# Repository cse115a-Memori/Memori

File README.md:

# File Structure

`./memori-app` - Tauri code

`./memori-dev` - ESP32 code

`./doc` - Documents for class

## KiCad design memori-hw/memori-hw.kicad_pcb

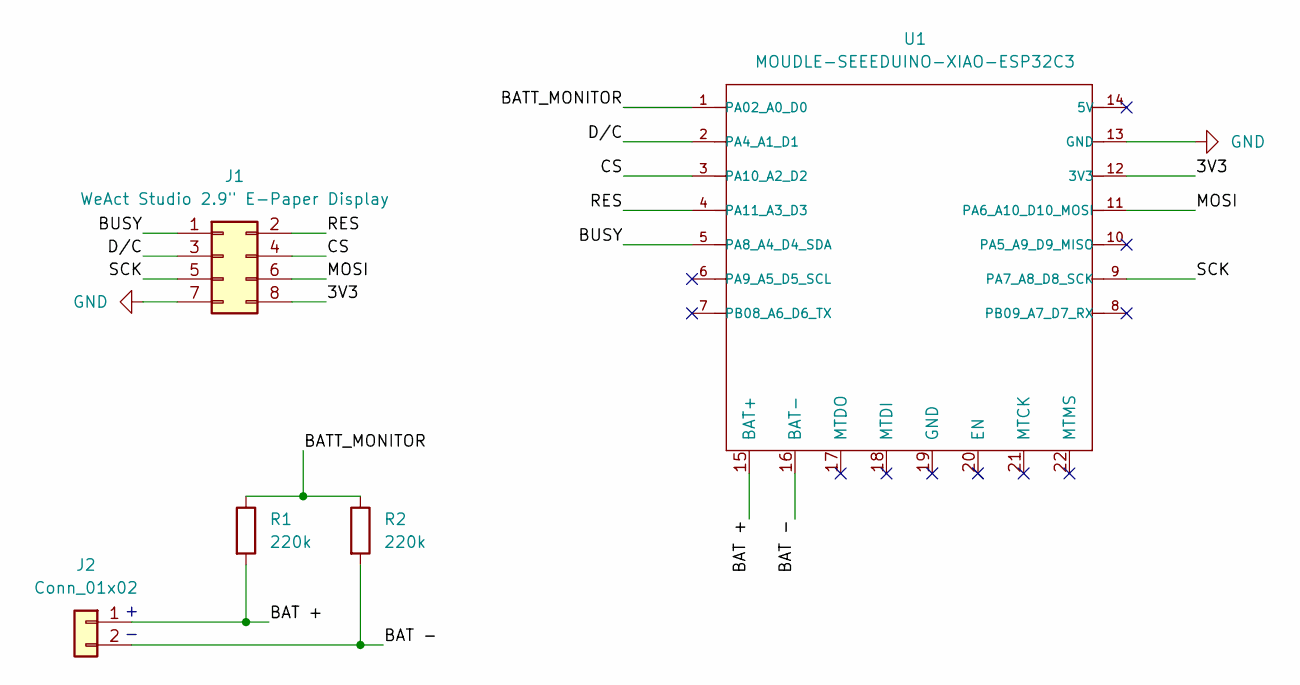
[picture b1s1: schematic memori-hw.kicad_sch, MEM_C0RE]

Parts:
J1: WeAct Studio 2.9" E-Paper Display; PinHeader_2x04_P2.54mm_Vertical
J2: Conn_01x02; JST_PH_S2B-PH-K_1x02_P2.00mm_Horizontal
R1, R2: 220k; R_Axial_DIN0204_L3.6mm_D1.6mm_P7.62mm_Horizontal
U1: MOUDLE-SEEEDUINO-XIAO-ESP32C3; XIAO-ESP32C3-SMD

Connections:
/3V3: J1.8, U1.12 (3V3)
/BAT +: J2.1, R1.2, U1.15 (BAT+)
/BAT -: J2.2, R2.2, U1.16 (BAT-)
/BATT_MONITOR: R1.1, R2.1, U1.1 (PA02_A0_D0)
/BUSY: J1.1, U1.5 (PA8_A4_D4_SDA)
/CS: J1.4, U1.3 (PA10_A2_D2)
/D/C: J1.3, U1.2 (PA4_A1_D1)
/MOSI: J1.6, U1.11 (PA6_A10_D10_MOSI)
/RES: J1.2, U1.4 (PA11_A3_D3)
/SCK: J1.5, U1.9 (PA7_A8_D8_SCK)
GND: J1.7, U1.13 (GND)

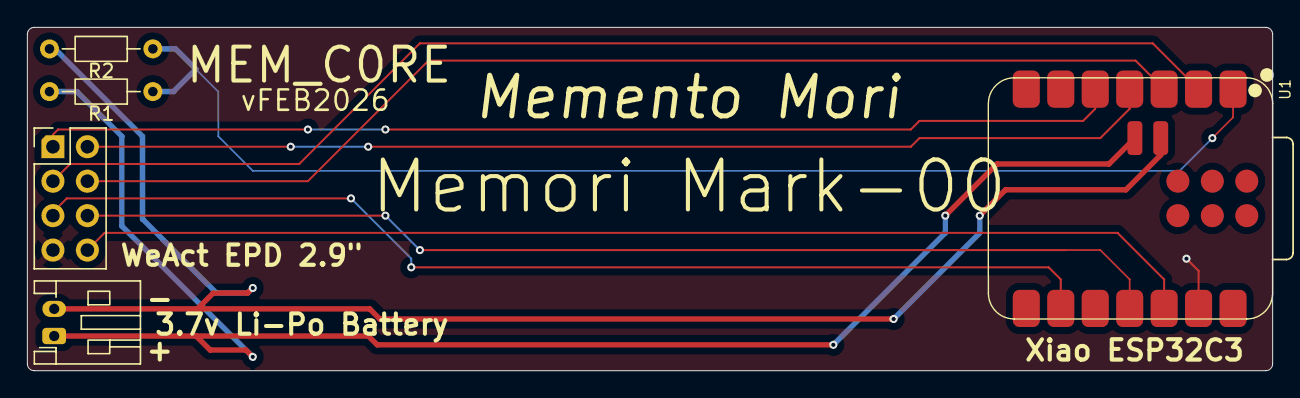
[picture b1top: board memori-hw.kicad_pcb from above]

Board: 4 copper layers, 91.8 x 25.3 mm, 5 parts (0 on the bottom side), 11 nets.

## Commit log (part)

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2026-01-09 added jj
2026-01-09 typst setup
2026-01-09 Added releaseplan files
2026-01-09 justfile
2026-01-10 esp project setup
2026-01-10 tauri setup
2026-01-10 tauri ios setup
2026-01-10 ESP32 setup
2026-01-10 justfile commands & readme
2026-01-10 setup mousefood
2026-01-11 fix readme & justfile
2026-01-11 setup svelte formatters
2026-01-11 new branch for me
2026-01-11 display hello world
2026-01-11 fixed typo
2026-01-14 Flake.nix
2026-01-15 Release plan
2026-01-16 more work on release plan
2026-01-17 finished with release plan
2026-01-17 example simulator
    basic simulator
2026-01-19 esp32c3 and simulator up and running
2026-01-19 restructuring
    something
2026-01-19 esp32c3 and simulator running memori
    pr fixes
2026-01-19 got tauri to run on ios device
2026-01-19 shadcn components
2026-01-20 fixed build errors and idomatic justfile
2026-01-20 added memori-transport
2026-01-21 add deepwiki badge
2026-01-23 display works on xiao
2026-01-25 taurpc
2026-01-25 svelte config fixup
2026-01-25 Added basic types for transport
2026-01-25 remade the memori-transport crates
2026-01-25 added the ble and websocket crates
2026-01-25 async traits
2026-01-25 setting up tcp transport
    we have some sort of communication so far
2026-01-25 async traits now constrain future to be boxed
2026-01-25 transport ble dependencies + esp ble test
2026-01-25 refactor tcp to be better
2026-01-25 tcp sim integration
2026-01-25 tcp app integration
2026-01-25 basic battery messaging
2026-01-25 patch fixes
2026-01-25 connect to simulator and get data back!
2026-01-26 fixes
2026-01-26 sprint1 plan
2026-01-28 Added Clock struct to widgets, and modified the esp update display function to properly increment the time
2026-01-28 Attempted to get the simulator to work with my widget. I think I am using the wrong commands to run it
2026-01-28 sprint1 report
2026-01-29 request_handler rework
2026-01-29 initial ble transport layer
    code enabling ble communication between the embedded board using
    transport/ble-device, and a host running the example binary provided
    through ble-host
    to test it out run the main binary on your board, then once it's
    advertising run the host-ble example "host"
2026-01-29 using oneshots
2026-01-29 rethink widget datamodel
2026-02-01 sprint 2 plan
2026-02-01 modified sprint 2 plan
2026-02-02 Added clock widget in current design
2026-02-02 Added clock to simulator's response to getBatteryLevel
2026-02-02 Added a bit of styling for the clock widget
2026-02-02 Delete memori-dev/memori/src/clock.rs
    I realized I had left this file in the branch on accident. It was from before we had the UI folder
2026-02-03 concurrent request support + refactoring
2026-02-04 non architecture dependant blepacket.id + other glorious ai suggested fixes
    title + typo fixes, no panicking in btleplug code, external timeout on
    devicebletransport
2026-02-04 more ergonomic external timeout for devicetransport
2026-02-04 ble interface
2026-02-04 device-side command concurrency
2026-02-04 remove cargo lock
2026-02-04 remove tracing
2026-02-05 initial run for local widget update task
2026-02-05 add device command and fix build for esp
2026-02-06 feat(memori-ui): Layout / Widget representation between app / device.
2026-02-06 fix compile for esp32
2026-02-06 refactor(memori-esp32): Refactor of BLE and UI for board.
2026-02-07 migrate to specta done
2026-02-07 remove unused test fn example
2026-02-07 dedup lib.rs imports
2026-02-07 cleanup and ble host import, to be implemented
2026-02-07 comment broken code out
2026-02-07 feat(memori-dev): Cancellable Refresh Tasks for Refreshable Widgets
2026-02-08 Esp now can spawn tasks to locally update any widget which sets local update frequency.
2026-02-08 fix(task-refrseh): Fixed static cell reinit issue via generation counter.
2026-02-09 learning dnd
2026-02-09 connecting app to board
2026-02-09 Local update frequency working with new widget framework. Will create a PR soon
2026-02-10 Removed extra logging statements
2026-02-10 Added github widget file. Need to flesh out rendering, and then work on state updating
2026-02-10 Github widget ui works for every layout. Need to consider what information we want to display though
2026-02-10 added bus and weather to tauri backend
2026-02-11 fixed specta in lib.rs for mobile, exclude type export
2026-02-11 connection type choice in app + ble-host cleanup
2026-02-11 sprint2 report and sprint3plan
2026-02-11 fix: Tauri send_name function now sends name.
2026-02-11 added layout and memoristate type export
2026-02-12 Adjusted dependencies
2026-02-12 Slight cleanup, added never variant to UpdateFrequency enum.
2026-02-12 Made clock borders the same as other widget borders
2026-02-12 added oauth flow
2026-02-12 removed file
2026-02-16 expose ble handler logic like tcp transport
2026-02-17 impl ble-host set state
2026-02-17 added commit graph to github widget. Need to slightly improve it and make sure it works for every layout.
2026-02-18 fixed typing issues in ble_host handler
2026-02-18 feat(hw): Init KiCad pcb design.
2026-02-18 oauth flow
2026-02-18 fixed 401 err with login
2026-02-19 very small changes to get app running without compile errors
2026-02-19 feat(hw): Finished with schematic.
2026-02-19 a lot of type gymnastics, dynamic layout done
2026-02-19 state scaffolding and dnd state, merged success with julian main
2026-02-19 generate bindings
2026-02-19 test run ios works
    checkpoint
2026-02-19 feat(hw): Finished non-battery PCB.
2026-02-20 Finished github widget UI
2026-02-20 Slight cleanup
2026-02-20 Made commits take an unsigned int because they can never be negative.
2026-02-20 Cleaned up some weird things that happened after merging the github widget.
2026-02-20 Removed unused imports and edited ble host_handler to utilize newer updatefrequency widgetKind member.
2026-02-20 feat(hw): Finished battery schematic.
2026-02-20 ios boot working, lots of refactoring
2026-02-21 simplify stores/services, extract location flow
2026-02-25 finalized sprint 3 report and sprint 4 plan
2026-02-25 revised
2026-02-26 added twitch
2026-02-26 small change to send_github
2026-02-28 refactor: gitignoring hw files.
2026-02-28 specta feature flags + suri fix(conn): name widget can now send to device and tcp
2026-02-28 tested to send widget payload over tcp and ble, simulator display update works, ble gets payload but no screen update
2026-02-28 scaffold connection update from rust, if ble wants to emit changes in connection state
2026-03-02 added github_data logic, need to finish up.
2026-03-02 refresh
2026-03-02 testing refresh over ble
2026-03-02 cargo path mismatch
2026-03-02 remove unused tcpconnection
2026-03-02 quick update
2026-03-02 per widget edit
2026-03-02 dnd logic bug fix
2026-03-02 break components apart, rename variables, combine widget + draft store
2026-03-02 edit each widget, refactor sortable item
2026-03-03 WidgetKind->Id, functions renamed and moved
2026-03-03 oauth refactor
2026-03-03 Trying my absolut best to get the test working. Realized I need to store Repo in tauri store in addition to username and auth token. Also, made the github widget repo not optional.
2026-03-03 accessed the tauri store from backend instead of frontend.
2026-03-04 changed test from getting commit frequency to refreshing the github widget.
2026-03-04 Cannot get stores from the backend.
2026-03-04 finally got auth token from store in the backend. Need to adjust the commit frequency array that I am receiving.
2026-03-04 need to fix commit frequency array
2026-03-05 Made sure to check all HTTP response status. Made helper function which all functions go through to actually do the HTTP requests.
2026-03-05 accidentally forgot to commit this to the PR, adding now
2026-03-05 tested app to run on ios phone, connects to esp over ble, set widget working, added some sound effects for connection success/failure
2026-03-05 add some sound effects
2026-03-05 feat/onboard: random device id generation on build stored statically
2026-03-06 feat/onboard: pairing widget displaying code
2026-03-06 feat/onboard: device advertises memori-{code}
2026-03-06 feat/onboard: app connects to memori-{code}
2026-03-06 add github persisted store
2026-03-06 initial ble refresh design impl
2026-03-06 mod dec i forgor from last commit
2026-03-06 Adjusted data.rs to utilize my refresh_github_widget function rather than the resolve_github_data function. Also made repo optional and handled cases where a user has not selected a repo yet.
2026-03-07 fixed dependency bug plus github login button.
2026-03-07 Finally got the frontend to receive updated information about current github login, and it reflects on the github widget tile.
2026-03-07 refactored github_data.rs to use a full_name repo rather than owner + repo strings. Also grabbed repo from Github store.
2026-03-07 Finalized github widget data resolution. Added dropdown menu for user's repos. Widget tile on frontend reflects choice.
2026-03-08 Added default for github_widget and stopped failing entire get_widget_kinds just for github fail.
2026-03-08 refactor
2026-03-08 modified Weather::new()
2026-03-08 modified oauth.rs
2026-03-08 added read:org to github auth scope
2026-03-08 refactor: organize documents
2026-03-08 feat: template for release summary
2026-03-08 feat: template for testplan
2026-03-08 feat: added all testable user stories to testplan
2026-03-08 simplify dnd logic, no cancel
2026-03-08 doc: worked on sprint4report, release-summary, testplan
2026-03-09 working on onboarding
2026-03-09 widget ui refactor
2026-03-09 updating but not rendering :(
2026-03-09 final commit before merge
2026-03-10 minimal onboard
    bg circle
    theme
2026-03-10 app working again, restore tauri-store version
2026-03-10 these are some fucky wucky changes
2026-03-10 ok we're here
2026-03-10 rust no compile error, app broken
2026-03-10 esp main typo fix
2026-03-10 pairing code
2026-03-10 feat/onboard: pairing code is now numeric
2026-03-10 sent working
2026-03-10 bus and weather
2026-03-11 feat/ui: HSplit, VSplit fixed
2026-03-11 device code saved, auto connects
2026-03-11 fix tauri store
2026-03-11 feat/ui: Only update display on state change
2026-03-11 tauri capabilities, work on phone
2026-03-11 refredebug + betr errors for ble-device
2026-03-11 debug the sequel
2026-03-11 "memori pairing code fix"
2026-03-13 Uncommented our other widgets, trying to debug to get more than github widget for demo
2026-03-13 fixed twitch, weather, and bus apis to actually get information and look clean on widget tiles. Made twitch filter out emojis from stream titles. Also made twitch widget only take 1 stream from the l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
2026-03-13 Added functions to change widget structs into memori widgets with hardcoded update frequencies. Our "with_minutes_update_frequency" didn't give us control over local vs remote.
2026-03-13 Fixed some layout bugs with github, clock, and weather widgets.
2026-03-14 Updated release summary with known issues (that I was able to find). Someone needs to add the acceptance criteria for the user stories.
2026-03-14 updated release summary/plan
2026-03-14 acceptance criteria
2026-03-16 feat: documents + dummy weather widget for demo
2026-03-18 Removed testing page code that wasn't commented out (it seems like we don't have a testing page lol). Also made reconnecting logic actually work with a retryConnection function. Previously, we had a 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
2026-03-18 OK... I adjusted our host-ble side of things so that BLE is much more consistent (and hopefully faster). Before, we were exclusively searching for the memori device in our host's cache, but if it was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
2026-03-18 slight adjustment to scan data.
2026-03-18 Made onboarding route to editor when finished rather than device, which no longer exists. Also made app disconnect from the device when the app is killed.
2026-03-18 Made bus widget use area of screen rather than hardcoded values for rendering.
2026-03-18 Made weather widget get live info
2026-03-18 There are so many print statements, im sorry... BLE should work more consistently on macOS now.
2026-03-19 feat/ble: each device now has a unique ble address
2026-03-19 Clock fix
